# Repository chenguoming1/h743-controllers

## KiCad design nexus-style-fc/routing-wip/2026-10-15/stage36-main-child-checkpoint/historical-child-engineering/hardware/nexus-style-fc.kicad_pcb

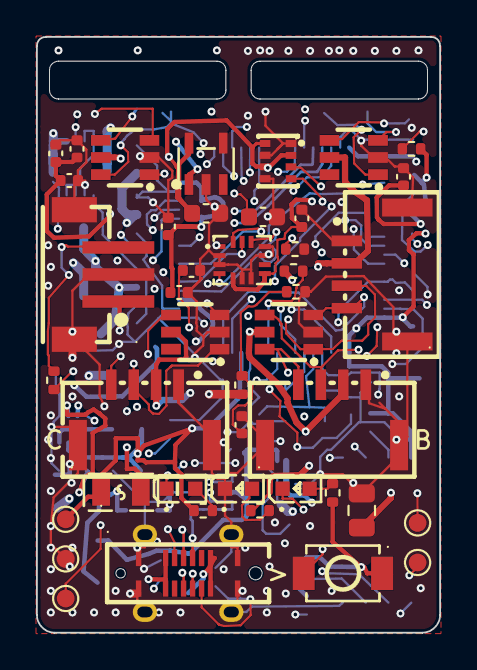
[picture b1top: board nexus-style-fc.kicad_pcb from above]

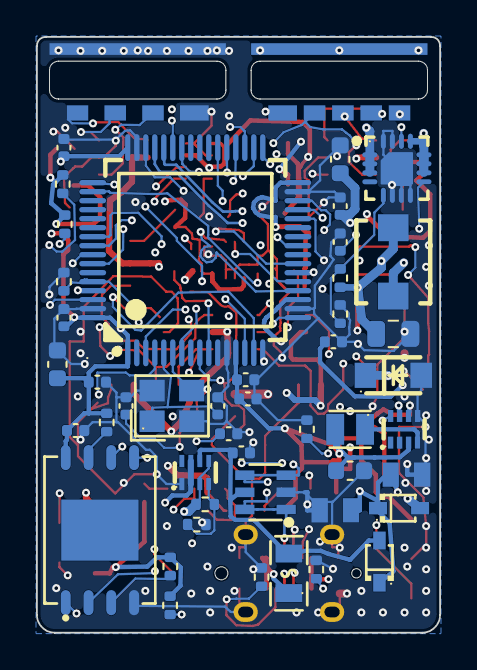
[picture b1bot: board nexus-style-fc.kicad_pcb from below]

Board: 6 copper layers, 22.4 x 33.1 mm, 89 parts (45 on the bottom side), 62 nets.

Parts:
C1, C2, C3, C4, C7, C8, C10, C13, C16, C17, C20, C22, C29, C30: 100nF; C_0402_1005Metric
C5, C9: 4.7uF; C_0603_1608Metric
C6, C18, C25: 1uF; C_0402_1005Metric
C11, C12: 30pF; C_0402_1005Metric
C14: 2.2uF; C_0402_1005Metric
C15: 10nF; C_0402_1005Metric
C19, C21: 10uF; C_0603_1608Metric
C23: 3.3nF; C_0402_1005Metric
C24, C26: 22uF; C_0805_2012Metric
C27, C31: 22uF; C_0805_2012Metric_Samsung_CL21_MinLand
C28: 22uF; C_0603_1608Metric
D1: LED1 yellow-green; LED0603-RD_GREEN__NexusMain_D1
D2: LED2 red; LED0603-RD_RED__NexusMain_D2
D3: Power LED blue; LED0603-RD_BLUE__NexusMain_D3
D4: SMF13A; SOD-123FL_L2.8-W1.8-LS3.6-RD
D5, D6: B5819WS; SOD-323_L1.8-W1.3-LS2.5-RD
F1, F2: 0.5A PTC; F0805
J1: Header child board; HeaderBoard_Joint
J2: DSM (UART1); CONN-SMD_B3B-ZR-SM4-TF
J3: A-CRSF (UART4); CONN-SMD_4P-P1.25_BM04B-GHS-TBT-LF-SN
J4: C (UART3); CONN-SMD_4P-P1.25_BM04B-GHS-TBT-LF-SN__NexusMain_J4
J5: B (UART6); CONN-SMD_4P-P1.25_BM04B-GHS-TBT-LF-SN
J6: USB-C vertical; USB-C-SMD_TYPE-C-31-D-06__NexusMain_J6
L1: 2.2uH 3A; IND-SMD_L4.6-W4.1
L2: 2.2uH; IND-SMD_L2.0-W1.6
R1, R5, R8, R9, R10, R17, R19: 10k; R_0402_1005Metric
R2, R3, R4, R22: 1k; R_0402_1005Metric
R6, R7: 2.2k; R_0402_1005Metric
R11: 120k; R_0402_1005Metric
R12: 22k; R_0402_1005Metric
R13: 100k; R_0402_1005Metric
R14: 27k; R_0402_1005Metric
R15: 27.4k; R_0402_1005Metric
R16: 52.3k; R_0402_1005Metric
R18: 21k; R_0402_1005Metric
R20, R21: 5.1k; R_0402_1005Metric
SW1: BOOT; SW-SMD_L3.9-W3.0-P4.45
TP1: SWDIO; TestPoint_Pad_D1.0mm
TP2: SWCLK; TestPoint_Pad_D1.0mm
TP3: 3V3; TestPoint_Pad_D1.0mm
TP4: GND; TestPoint_Pad_D1.0mm
TP5: NRST; TestPoint_Pad_D1.0mm
U1: STM32F722RET6; LQFP-64_L10.0-W10.0-P0.50-LS12.0-BL
U2: ICM-42688-P; LGA-14_L3.0-W2.5-P0.50-TL
U3: DPS368XTSA1; LGA-8_L2.5-W2.0-P0.65-TR_DPS368
U4: W25N01GVZEIG; WSON-8_L8.0-W6.10-P1.27-BL-EP
U5: TPS62130RGTR; QFN-16_L3.0-W3.0-P0.50-TL-EP1.7
U7: USBLC6-2SC6; SOT-23-6_L2.9-W1.6-P0.95-LS2.8-BL
U9: TPS2116DRLR; SOT-583-8_L2.1-W1.6-P0.50-LS1.6-BL
U10: TPS70933DBVR; SOT-23-5_L3.0-W1.7-P0.95-LS2.8-BL
U11, U12, U13, U15: SRV05-4; SOT-23-6_L2.9-W1.6-P0.95-LS2.8-BR
U14: TPS629210DRLR; SOT-5X3-8_L2.1-W1.2-P0.50-LS1.6-BL_DRL0008A
Y1: 8MHz 20pF; CRYSTAL-SMD_4P-L3.2-W2.5-BL

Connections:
3V3: C1.1, C2.1, C3.1, C4.1, C5.1, C6.1, C7.1, C8.1, C20.1, C28.1, F2.1, L2.2, R2.1, R3.1, R8.2, R9.2, R10.2, SW1.2, TP3.1, U1.1, U1.13, U1.19, U1.32, U1.48, U1.64, U4.8, U14.3
3V3_DSM: F2.2, J2.1
3V3_SENS: C13.1, C14.1, C15.1, C16.1, C17.1, C19.1, R5.2, R6.2, R7.2, U2.5, U2.8, U3.2, U3.6, U3.8, U10.5
5V: C26.1, J3.2, J4.2, J5.2, R4.1, R18.1, U9.2, U9.7, U11.5, U12.5, U13.5, U15.5
5V_BUCK: C24.1, L1.2, R11.1, R13.1, U5.14, U9.3, U9.5
5V_SENSE: C30.1, R18.2, R19.1, U1.10
A_RX: J3.3, U1.14, U13.1
A_TX: J3.4, U1.15, U13.3
BOOT0: R1.1, SW1.1, U1.60
B_RX: J5.3, U1.37, U13.4
B_TX: J5.4, U1.38, U13.6
CC1: J6.A5, R20.1
CC2: J6.B5, R21.1
C_RX: J4.3, U1.28, U15.1
C_TX: J4.4, U1.29, U15.3
DSM_DATA: J2.3, R22.2, U1.43, U15.4
DSM_TX: R22.1, U1.42
ESC: J1.5, U1.58, U11.4
FB_5V: R11.2, R12.1, U5.5
FLASH_CS: R8.1, U1.33, U4.1
FLASH_HOLD: R10.1, U4.7
FLASH_WP: R9.1, U4.3
GND: C1.2, C2.2, C3.2, C4.2, C5.2, C6.2, C7.2, C8.2, C9.2, C10.2, C11.2, C12.2, C13.2, C14.2, C15.2, C16.2, C17.2, C18.2, C19.2, C20.2, C21.2, C22.2, C23.2, C24.2, C25.2, C26.2, C27.2, C28.2, C29.2, C30.2, C31.2, D3.1, D4.2, J1.2, J2.2, J2.4, J2.5, J3.1, J3.5, J3.6, J4.1, J4.5, J4.6, J5.1, J5.5, J5.6, J6.A1, J6.A12, J6.B1, J6.B12, J6.EP, R1.2, R12.2, R14.2, R15.2, R17.2, R19.2, R20.2, R21.2, TP4.1, U1.12, U1.18, U1.31, U1.47, U1.63, U2.2, U2.3, U2.6, U2.7, U2.10, U2.11, U3.1, U3.5, U3.7, U4.4, U5.6, U5.7, U5.8, U5.15, U5.16, U5.17, U7.2, U9.1, U10.2, U11.2, U12.2, U13.2, U14.5, U15.2, Y1.2, Y1.4
I2C1_SCL: R6.1, U1.61, U3.4
I2C1_SDA: R7.1, U1.62, U3.3
IMU_CS: R5.1, U1.20, U2.12
IMU_INT: U1.50, U2.4
LED1_A: D1.2, R2.2
LED1_K: D1.1, U1.3
LED2_A: D2.2, R3.2
LED2_K: D2.1, U1.4
LED3_A: D3.2, R4.2
NRST: C10.1, TP5.1, U1.7
OSC_IN: C11.1, U1.5, Y1.1
OSC_OUT: C12.1, U1.6, Y1.3
PR1: R13.2, R14.1, U9.4
RPM: J1.4, U1.16, U11.3
S1: J1.9, U1.56, U12.4
S2: J1.8, U1.57, U12.3
S3: J1.7, U1.25, U12.1
SBUS: J1.3, U1.17, U11.1
SCONF: R15.1, U14.8
SPI1_MISO: U1.22, U2.1
SPI1_MOSI: U1.23, U2.14
SPI1_SCK: U1.21, U2.13
SPI2_MISO: U1.35, U4.2
SPI2_MOSI: U1.36, U4.5
SPI2_SCK: U1.34, U4.6
SS_5V: C23.1, U5.9
SWCLK: TP2.1, U1.49
SWDIO: TP1.1, U1.46
SW_3V3: L2.1, U14.4
SW_5V: L1.1, U5.1, U5.2, U5.3
TAIL: J1.6, U1.55, U11.6
USB_DM: J6.A7, J6.B7, U1.44, U7.1, U7.6
USB_DP: J6.A6, J6.B6, U1.45, U7.3, U7.4
VBUS: C25.1, D6.2, F1.2, U7.5, U9.6
VBUS_C: F1.1, J6.A4, J6.A9, J6.B4, J6.B9
VCAP: C9.1, U1.30
VSYS: C18.1, C27.1, C31.1, D5.1, D6.1, U10.1, U14.6, U14.7
VX: C21.1, C22.1, D4.1, D5.2, J1.1, R16.1, U5.10, U5.11, U5.12, U5.13
VX_SENSE: C29.1, R16.2, R17.1, U1.9

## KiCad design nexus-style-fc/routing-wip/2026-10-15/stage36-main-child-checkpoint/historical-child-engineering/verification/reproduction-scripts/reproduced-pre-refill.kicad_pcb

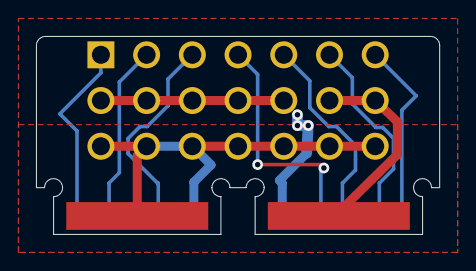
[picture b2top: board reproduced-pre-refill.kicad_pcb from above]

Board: 2 copper layers, 22.4 x 11.0 mm, 12 parts (0 on the bottom side), 9 nets.

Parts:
J1: Servo header 3x7; Header_3x07_P2.54_Vertical_Servo
K1: GND strip; ChildBoard_TabStrip_W7.892
K2: VX strip; ChildBoard_TabStrip_W7.892
P1: S1 tab pad; ChildBoard_TabPad_Sig
P2: S2 tab pad; ChildBoard_TabPad_Sig
P3: S3 tab pad; ChildBoard_TabPad_Sig
P4: TAIL tab pad; ChildBoard_TabPad_Sig
P5: ESC tab pad; ChildBoard_TabPad_Sig
P6: RPM tab pad; ChildBoard_TabPad_Sig
P7: SBUS tab pad; ChildBoard_TabPad_Sig
T1: GND tab pad; ChildBoard_TabPad_Pwr
T2: VX tab pad; ChildBoard_TabPad_Pwr

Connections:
ESC: J1.13, P5.1
GND: J1.3, J1.6, J1.9, J1.12, J1.15, J1.18, J1.21, K1.1, T1.1
RPM: J1.16, P6.1
S1: J1.1, P1.1
S2: J1.4, P2.1
S3: J1.7, P3.1
SBUS: J1.19, P7.1
TAIL: J1.10, P4.1
VX: J1.2, J1.5, J1.8, J1.11, J1.14, J1.17, J1.20, K2.1, T2.1
